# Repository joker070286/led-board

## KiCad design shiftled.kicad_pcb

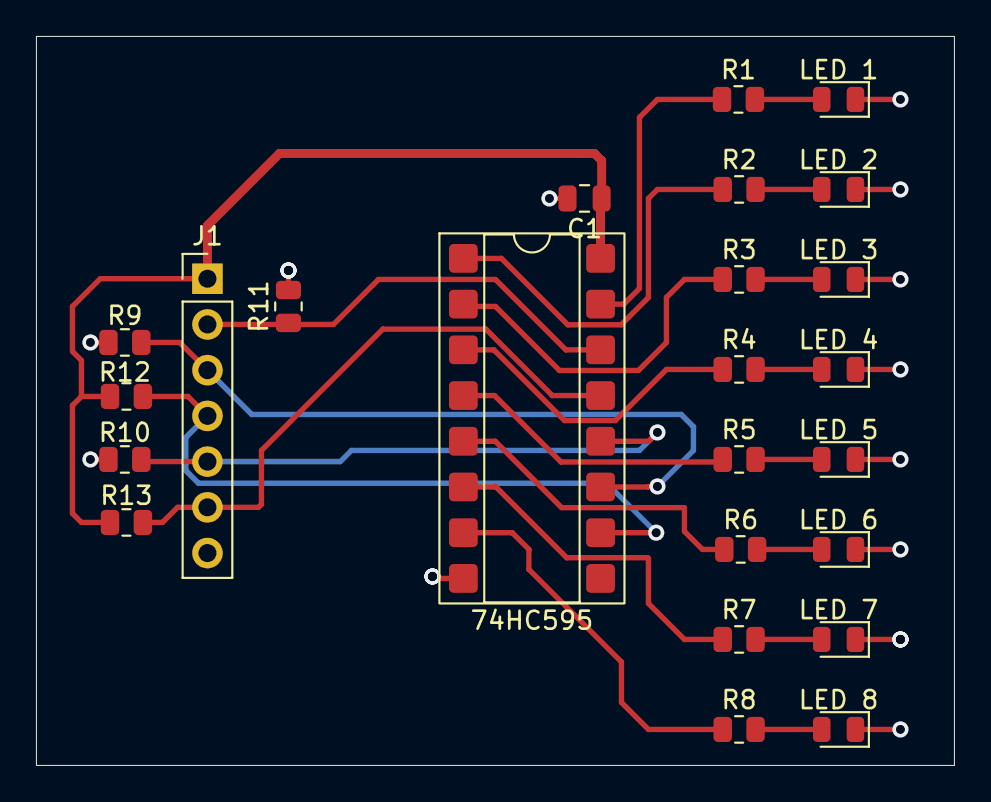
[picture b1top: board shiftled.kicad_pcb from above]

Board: 2 copper layers, 51.0 x 40.5 mm, 24 parts (0 on the bottom side), 23 nets.

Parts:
C1: 100nF; C_0805_2012Metric
D1: LED 1; LED_0805_2012Metric
D2: LED 2; LED_0805_2012Metric
D3: LED 3; LED_0805_2012Metric
D4: LED 4; LED_0805_2012Metric
D5: LED 5; LED_0805_2012Metric
D6: LED 6; LED_0805_2012Metric
D7: LED 7; LED_0805_2012Metric
D8: LED 8; LED_0805_2012Metric
J1: Conn_01x07_Pin; PinHeader_1x07_P2.54mm_Vertical
R1, R2, R3, R4, R5, R6, R7, R8: 470; R_0805_2012Metric
R9, R10, R11, R12, R13: 100k; R_0805_2012Metric
U1: 74HC595; DIP-16_W7.62mm_SMDSocket_SmallPads

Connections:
+5V: C1.1, J1.1, R9.1, R10.1, U1.16 (VCC)
GND: C1.2, D1.1 (K), D2.1 (K), D3.1 (K), D4.1 (K), D5.1 (K), D6.1 (K), D7.1 (K), D8.1 (K), J1.7, R11.2, R12.2, R13.2, U1.8 (GND)
unnamed: D1.2 (A), R1.2
unnamed: D2.2 (A), R2.2
unnamed: D3.2 (A), R3.2
unnamed: D4.2 (A), R4.2
unnamed: D5.2 (A), R5.2
unnamed: D6.2 (A), R6.2
unnamed: D7.2 (A), R7.2
unnamed: D8.2 (A), R8.2
unnamed: J1.2, R11.1, U1.14 (SER)
unnamed: J1.3, R12.1, U1.11 (SRCLK)
unnamed: J1.4, R9.2, U1.10 (~SRCLR)
unnamed: J1.5, R13.1, U1.12 (RCLK)
unnamed: J1.6, R10.2, U1.13 (~OE)
unnamed: R1.1, U1.15 (QA)
unnamed: R2.1, U1.1 (QB)
unnamed: R3.1, U1.2 (QC)
unnamed: R4.1, U1.3 (QD)
unnamed: R5.1, U1.4 (QE)
unnamed: R6.1, U1.5 (QF)
unnamed: R7.1, U1.6 (QG)
unnamed: R8.1, U1.7 (QH)

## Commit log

2026-05-07 create project
2026-05-07 add shiftregister footprint
2026-05-14 add part
2026-05-14 add netlist
2026-05-14 add pcb
2026-05-15 move capasitor
2026-05-15 routing parts
2026-05-17 remvoed backup files
2026-05-17 remove backup files
